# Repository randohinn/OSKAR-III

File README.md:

# Oskar III
 AHHAA robotmaskott Oskar III riist- ja tarkvara

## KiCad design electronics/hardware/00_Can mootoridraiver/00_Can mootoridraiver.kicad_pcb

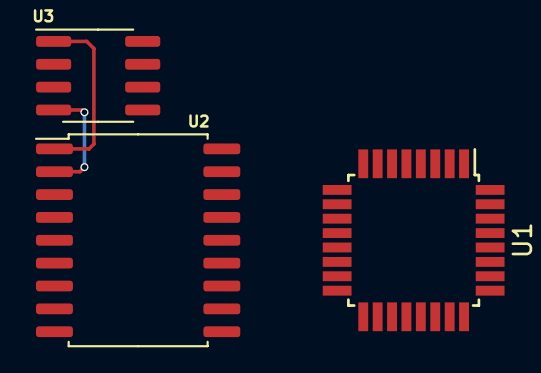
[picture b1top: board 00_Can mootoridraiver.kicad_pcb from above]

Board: 2 copper layers, 3 parts (0 on the bottom side), 9 nets.

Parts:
U1: ATmega328P-AU; TQFP-32_7x7mm_P0.8mm
U2: MCP2515-xSO; SOIC-18W_7.5x11.6mm_P1.27mm
U3: MCP2561-E-P; SOIC-8_3.9x4.9mm_P1.27mm

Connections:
+5V: U1.4, U1.6, U1.18, U2.18, U3.3
CLKOUT: U1.7, U2.3
GND: U1.3, U1.5, U1.21, U2.9, U3.2
MISO: U1.16, U2.15
MOSI: U1.15, U2.14
RXCAN: U2.2, U3.4
SCK: U1.17, U2.13
SS: U1.14, U2.16
TXCAN: U2.1, U3.1

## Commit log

2020-11-08 CAN Driver'i väga robustne skeem
2020-11-11 CAN'i firmware algus
2020-11-15 CAN'i kontrolleri registriaadresside definitsioonid.
2020-11-18 Buildfailid eemaldatud repost.
2020-11-20 Kõigi MCP2515 registrite definitsioonid
2020-11-20 Lisatud uued SPI funktsioonid mitme operatsiooni läbiviimiseks sama CS tsükli sees
2020-11-20 Alustame MCP2515 funktsioonide loomist
2020-11-20 Funktsionaalsus MCP2515 Töörežiimi vahetamiseks ja CLKOUT lubamiseks/keelamiseks
2020-11-24 Viime CAN kontrolleri käivitumisel konfiguratisoonirežiimi
2020-12-01 Siit võiks saada CAN väljundit
2020-12-03 CAN robustsemaks - ei töötanud
2020-12-04 Uuendatud skeem uue CAN driveri kiibiga
2020-12-04 CAN driveri footprint
2020-12-04 CAN konf 1Mbps peale, GYEMS'iga suheldes selgus, et kasutavad seda bitrate'i
2020-12-05 CANi kallal tööd.
2020-12-07 NAK'i andev CAN id skanneriga
2020-12-13 CAN'i mõni väiksem mittemõjutav muudatus bitiväärtustesse
2020-12-19 Alustame ROS-i poole arendamist
2020-12-19 catkin_make töötab ja draiverit saab käivitada
2020-12-19 Litsents juurkausta
2021-01-03 Add Boilerplate for Serial comms and Plugin architecture
2021-01-04 Hardware: Small CAN change, start Distance tester project for IR/US/LIDAR comparisons this week.
